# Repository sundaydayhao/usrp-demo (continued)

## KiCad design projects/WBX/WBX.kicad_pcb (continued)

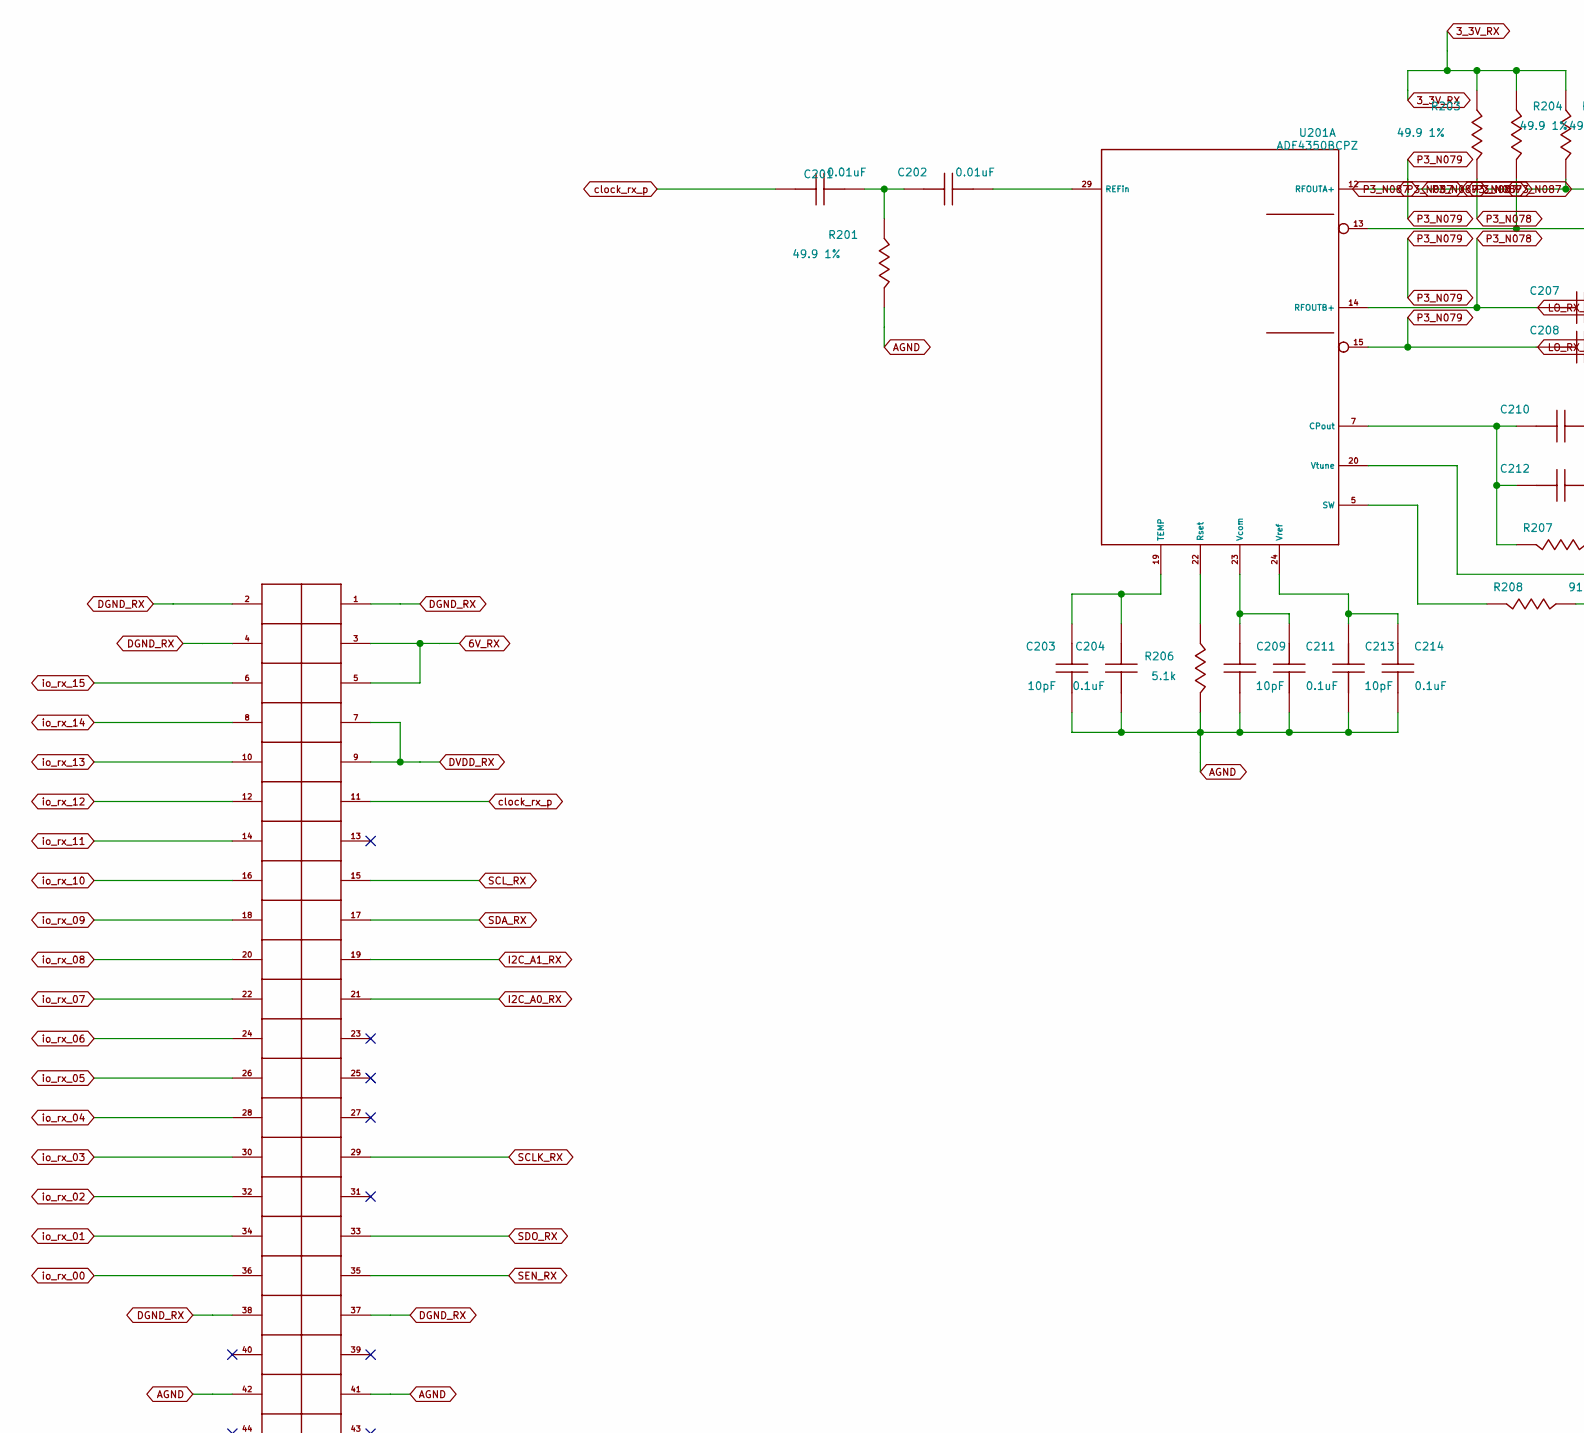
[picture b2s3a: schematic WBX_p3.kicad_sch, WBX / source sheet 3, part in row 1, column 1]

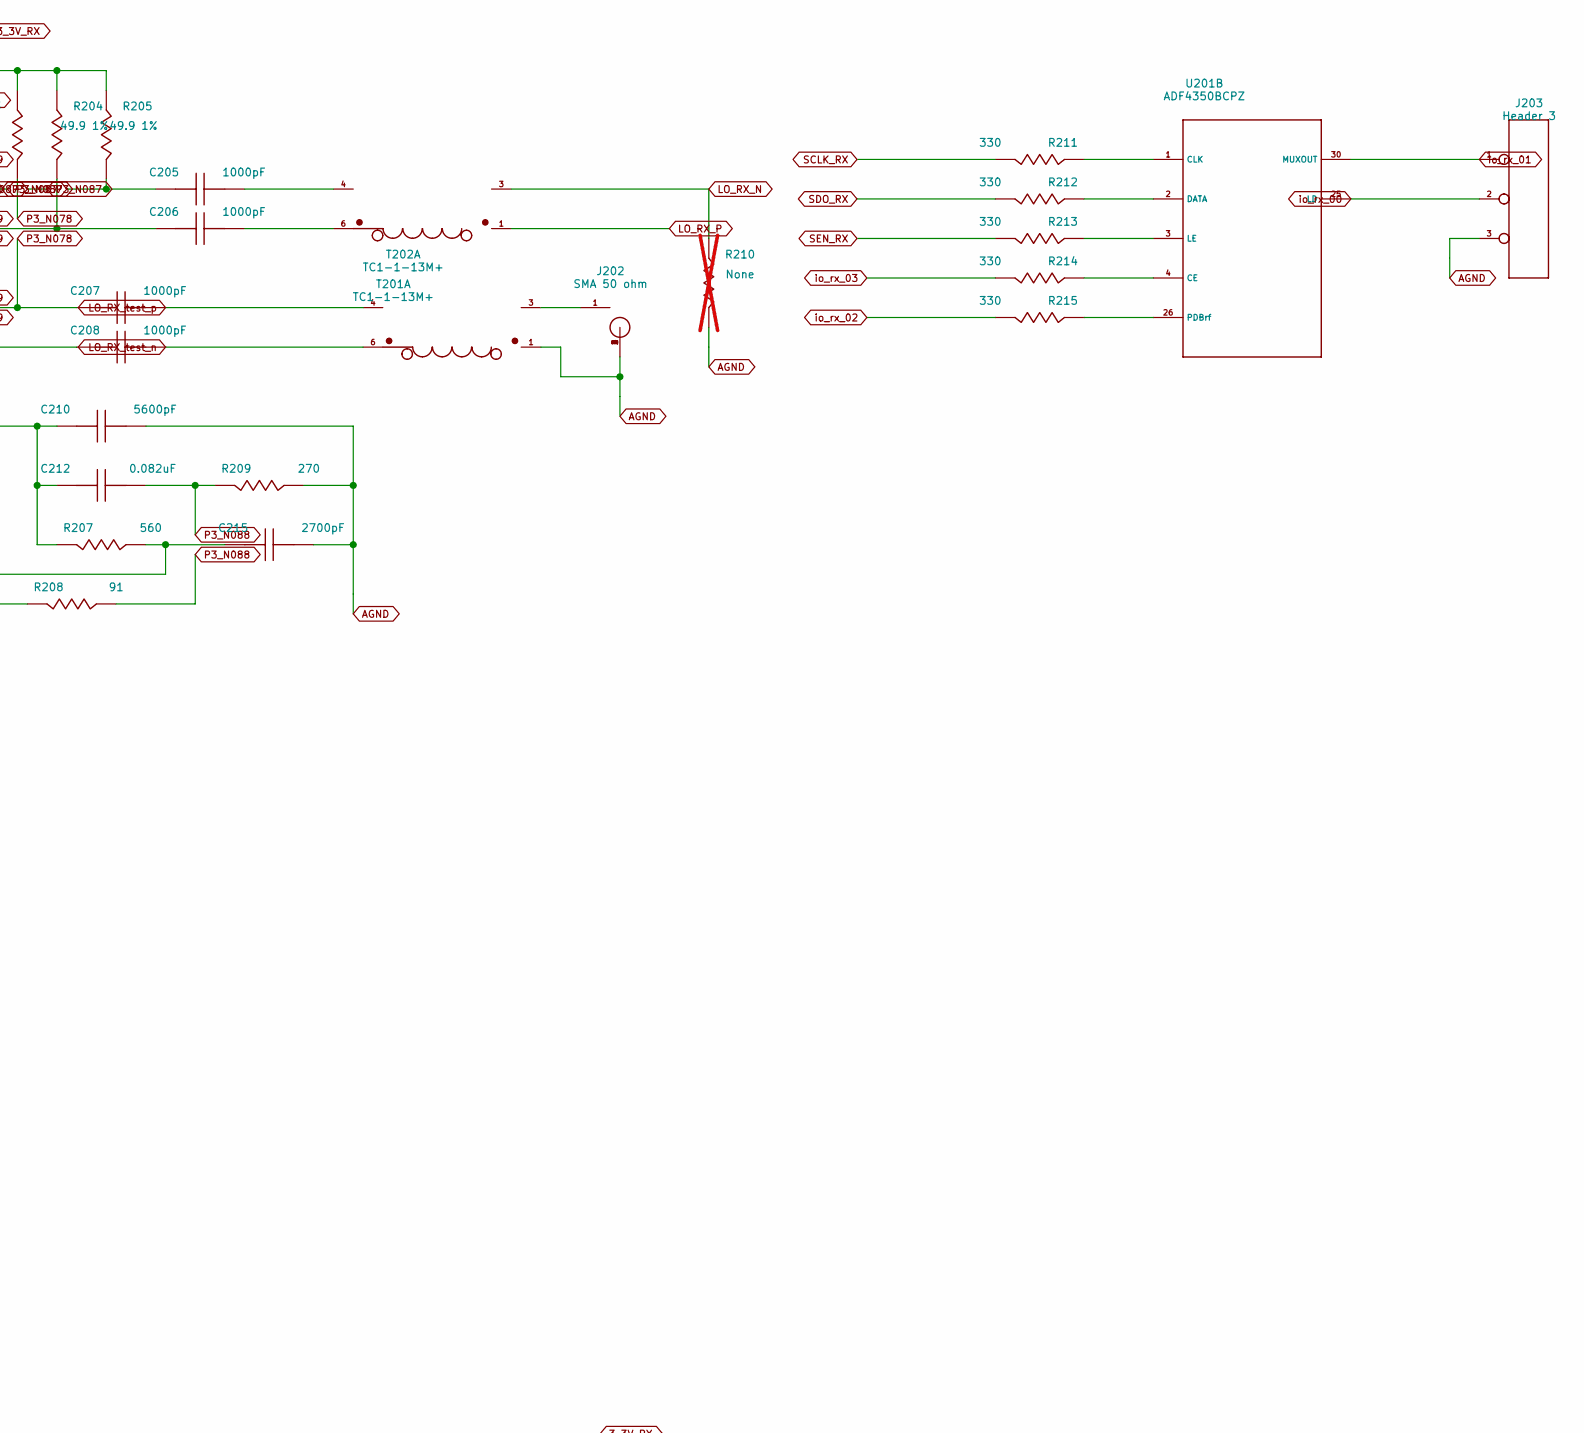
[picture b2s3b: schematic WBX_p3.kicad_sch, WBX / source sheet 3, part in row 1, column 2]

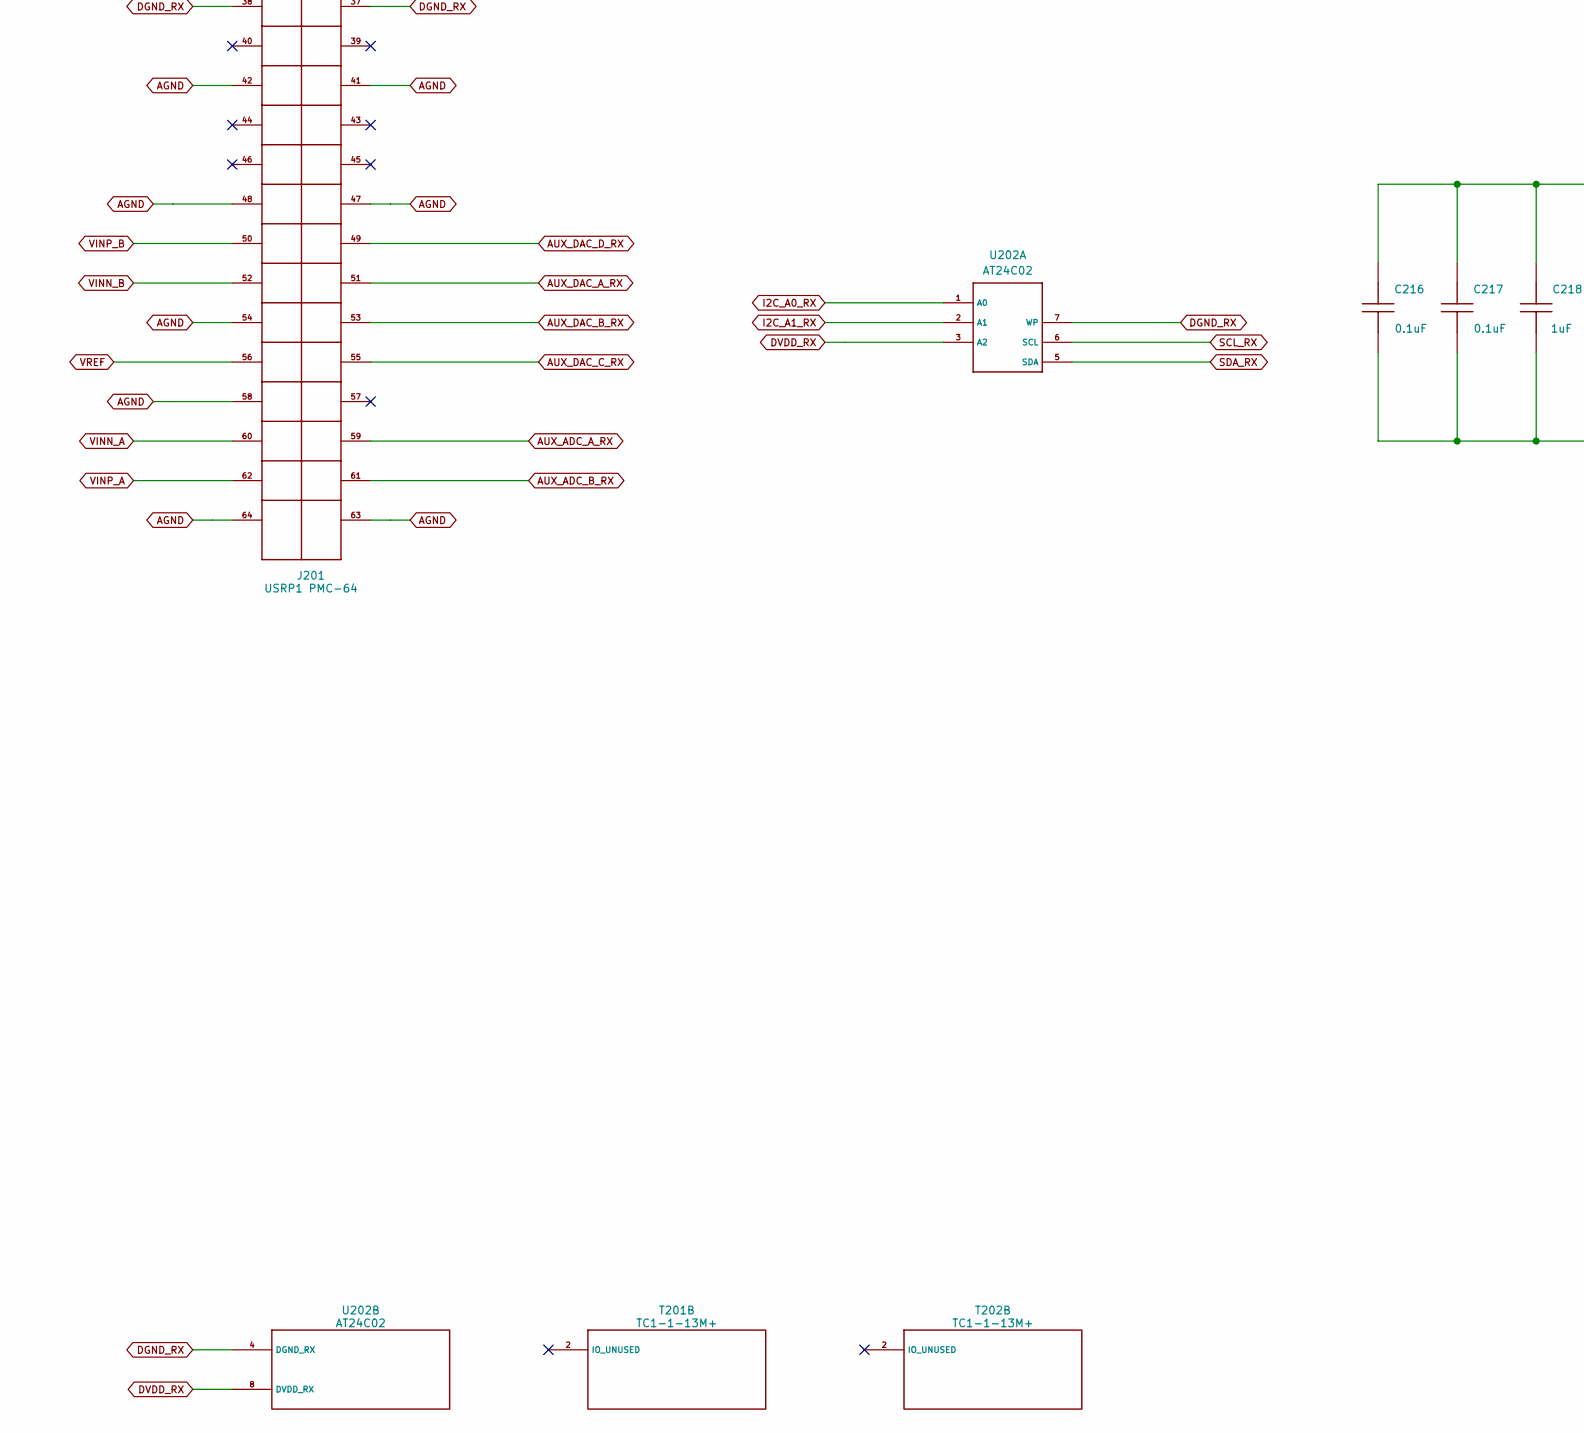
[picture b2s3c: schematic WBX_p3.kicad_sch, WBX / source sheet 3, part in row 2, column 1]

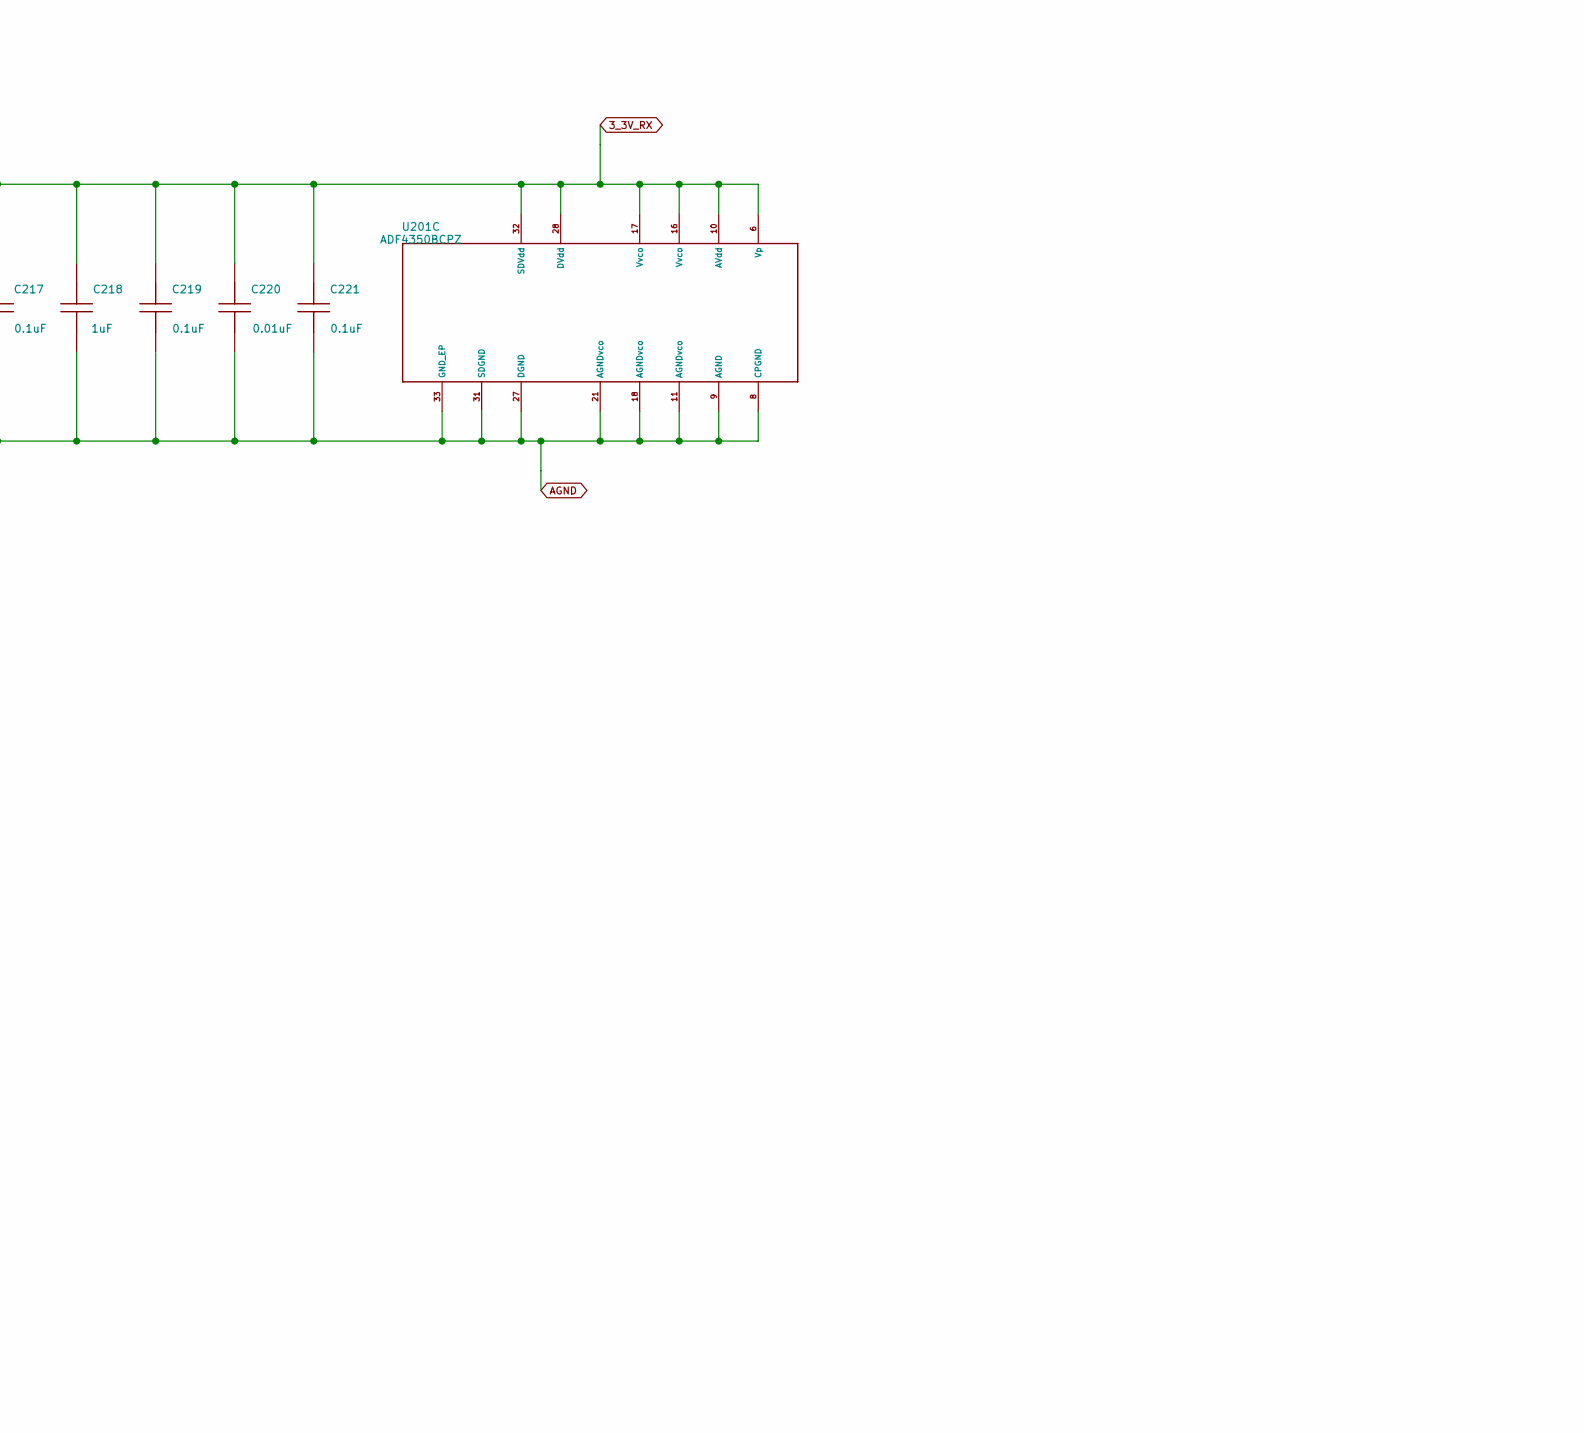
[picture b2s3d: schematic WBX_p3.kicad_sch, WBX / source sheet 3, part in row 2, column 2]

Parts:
C201: 0.01uF; C201
C202: 0.01uF; C202
C203: 10pF; C203
C204: 0.1uF; C204
C205: 1000pF; C205
C206: 1000pF; C206
C207: 1000pF; C207
C208: 1000pF; C208
C209: 10pF; C209
C210: 5600pF; C210
C211: 0.1uF; C211
C212: 0.082uF; C212
C213: 10pF; C213
C214: 0.1uF; C214
C215: 2700pF; C215
C216: 0.1uF; C216; MPN CL05B104KO5NNNC; LCSC C1525
C217: 0.1uF; C217; MPN CL05B104KO5NNNC; LCSC C1525
C218: 1uF; C218
C219: 0.1uF; C219; MPN CL05B104KO5NNNC; LCSC C1525
C220: 0.01uF; C220
C221: 0.1uF; C221; MPN CL05B104KO5NNNC; LCSC C1525
J201: USRP1 PMC-64; J201
J202: SMA 50 ohm; J202
J203: Header 3; J203
R201: 49.9 1%; R201
R203: 49.9 1%; R203
R204: 49.9 1%; R204
R205: 49.9 1%; R205
R206: 5.1k; R206
R207: 560; R207
R208: 91; R208
R209: 270; R209
R210: None; R210; not fitted
R211: 330; R211
R212: 330; R212
R213: 330; R213
R214: 330; R214
R215: 330; R215
T201: TC1-1-13M+; T201; MPN TC1-1-13M+
T202: TC1-1-13M+; T202; MPN TC1-1-13M+
U201: ADF4350BCPZ; U201; MPN ADF4350BCPZ
U202: AT24C02; U202; MPN AT24C02C-SSHM-T; LCSC C6203

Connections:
3_3V_RX: C216.1, C217.1, C218.1, C219.1, C220.1, C221.1, R203.1, R204.1, R205.1, U201.6 (Vp), U201.10 (AVdd), U201.16 (Vvco), U201.17 (Vvco), U201.28 (DVdd), U201.32 (SDVdd); also elsewhere on the board
6V_RX: J201.3, J201.5; also elsewhere on the board
AGND: C203.2, C204.2, C209.2, C210.1, C211.2, C213.2, C214.2, C215.1, C216.2, C217.2, C218.2, C219.2, C220.2, C221.2, J201.41, J201.42, J201.47, J201.48, J201.54, J201.58, J201.63, J201.64, J202.2, J202.3, J202.4, J202.5, J203.3, R201.2, R206.2, R209.1, R210.2, T201.1, U201.8 (CPGND), U201.9 (AGND), U201.11 (AGNDvco), U201.18 (AGNDvco), U201.21 (AGNDvco), U201.27 (DGND), U201.31 (SDGND), U201.33 (GND_EP); also elsewhere on the board
AUX_ADC_A_RX: J201.59; also elsewhere on the board
AUX_ADC_B_RX: J201.61
AUX_DAC_A_RX: J201.51
AUX_DAC_B_RX: J201.53
AUX_DAC_C_RX: J201.55; also elsewhere on the board
AUX_DAC_D_RX: J201.49
DGND_RX: J201.1, J201.2, J201.4, J201.37, J201.38, U202.4 (DGND_RX), U202.7 (WP)
DVDD_RX: J201.7, J201.9, U202.3 (A2), U202.8 (DVDD_RX)
I2C_A0_RX: J201.21, U202.1 (A0)
I2C_A1_RX: J201.19, U202.2 (A1)
LO_RX_N: R210.1, T202.3; also elsewhere on the board
LO_RX_P: T202.1; also elsewhere on the board
LO_RX_test_n: C208.1, T201.6
LO_RX_test_p: C207.1, T201.4
unnamed: C201.1, C202.2, R201.1
unnamed: C205.1, T202.4
unnamed: C206.1, T202.6
unnamed: C206.2, R204.2, U201.13
unnamed: J202.1, T201.3
unnamed: C210.2, C212.2, R207.2, U201.7 (CPout)
unnamed: C202.1, U201.29 (REFin)
unnamed: R206.1, U201.22 (Rset)
unnamed: R208.2, U201.5 (SW)
unnamed: C203.1, C204.1, U201.19 (TEMP)
unnamed: C209.1, C211.1, U201.23 (Vcom)
unnamed: C213.1, C214.1, U201.24 (Vref)
unnamed: C215.2, R207.1, U201.20 (Vtune)
unnamed: R214.1, U201.4 (CE)
unnamed: R211.1, U201.1 (CLK)
unnamed: R212.1, U201.2 (DATA)
unnamed: R213.1, U201.3 (LE)
unnamed: R215.1, U201.26 (PDBrf)
P3_N078: C207.2, R203.2, U201.14 (RFOUTB+)
P3_N079: C208.2, U201.15
P3_N087: C205.2, R205.2, U201.12 (RFOUTA+)
P3_N088: C212.1, R208.1, R209.2
SCLK_RX: J201.29, R211.2
SCL_RX: J201.15, U202.6 (SCL)
SDA_RX: J201.17, U202.5 (SDA)
SDO_RX: J201.33, R212.2
SEN_RX: J201.35, R213.2
VINN_A: J201.60; also elsewhere on the board
VINN_B: J201.52; also elsewhere on the board
VINP_A: J201.62; also elsewhere on the board
VINP_B: J201.50; also elsewhere on the board
VREF: J201.56; also elsewhere on the board
clock_rx_p: C201.2, J201.11
io_rx_00: J201.36, J203.2, U201.25 (LD)
io_rx_01: J201.34, J203.1, U201.30 (MUXOUT)
io_rx_02: J201.32, R215.2
io_rx_03: J201.30, R214.2
io_rx_04: J201.28; also elsewhere on the board
io_rx_05: J201.26; also elsewhere on the board
io_rx_06: J201.24; also elsewhere on the board
io_rx_07: J201.22; also elsewhere on the board
io_rx_08: J201.20; also elsewhere on the board
io_rx_09: J201.18; also elsewhere on the board
io_rx_10: J201.16; also elsewhere on the board
io_rx_11: J201.14; also elsewhere on the board
io_rx_12: J201.12; also elsewhere on the board
io_rx_13: J201.10; also elsewhere on the board
io_rx_14: J201.8; also elsewhere on the board
io_rx_15: J201.6; also elsewhere on the board

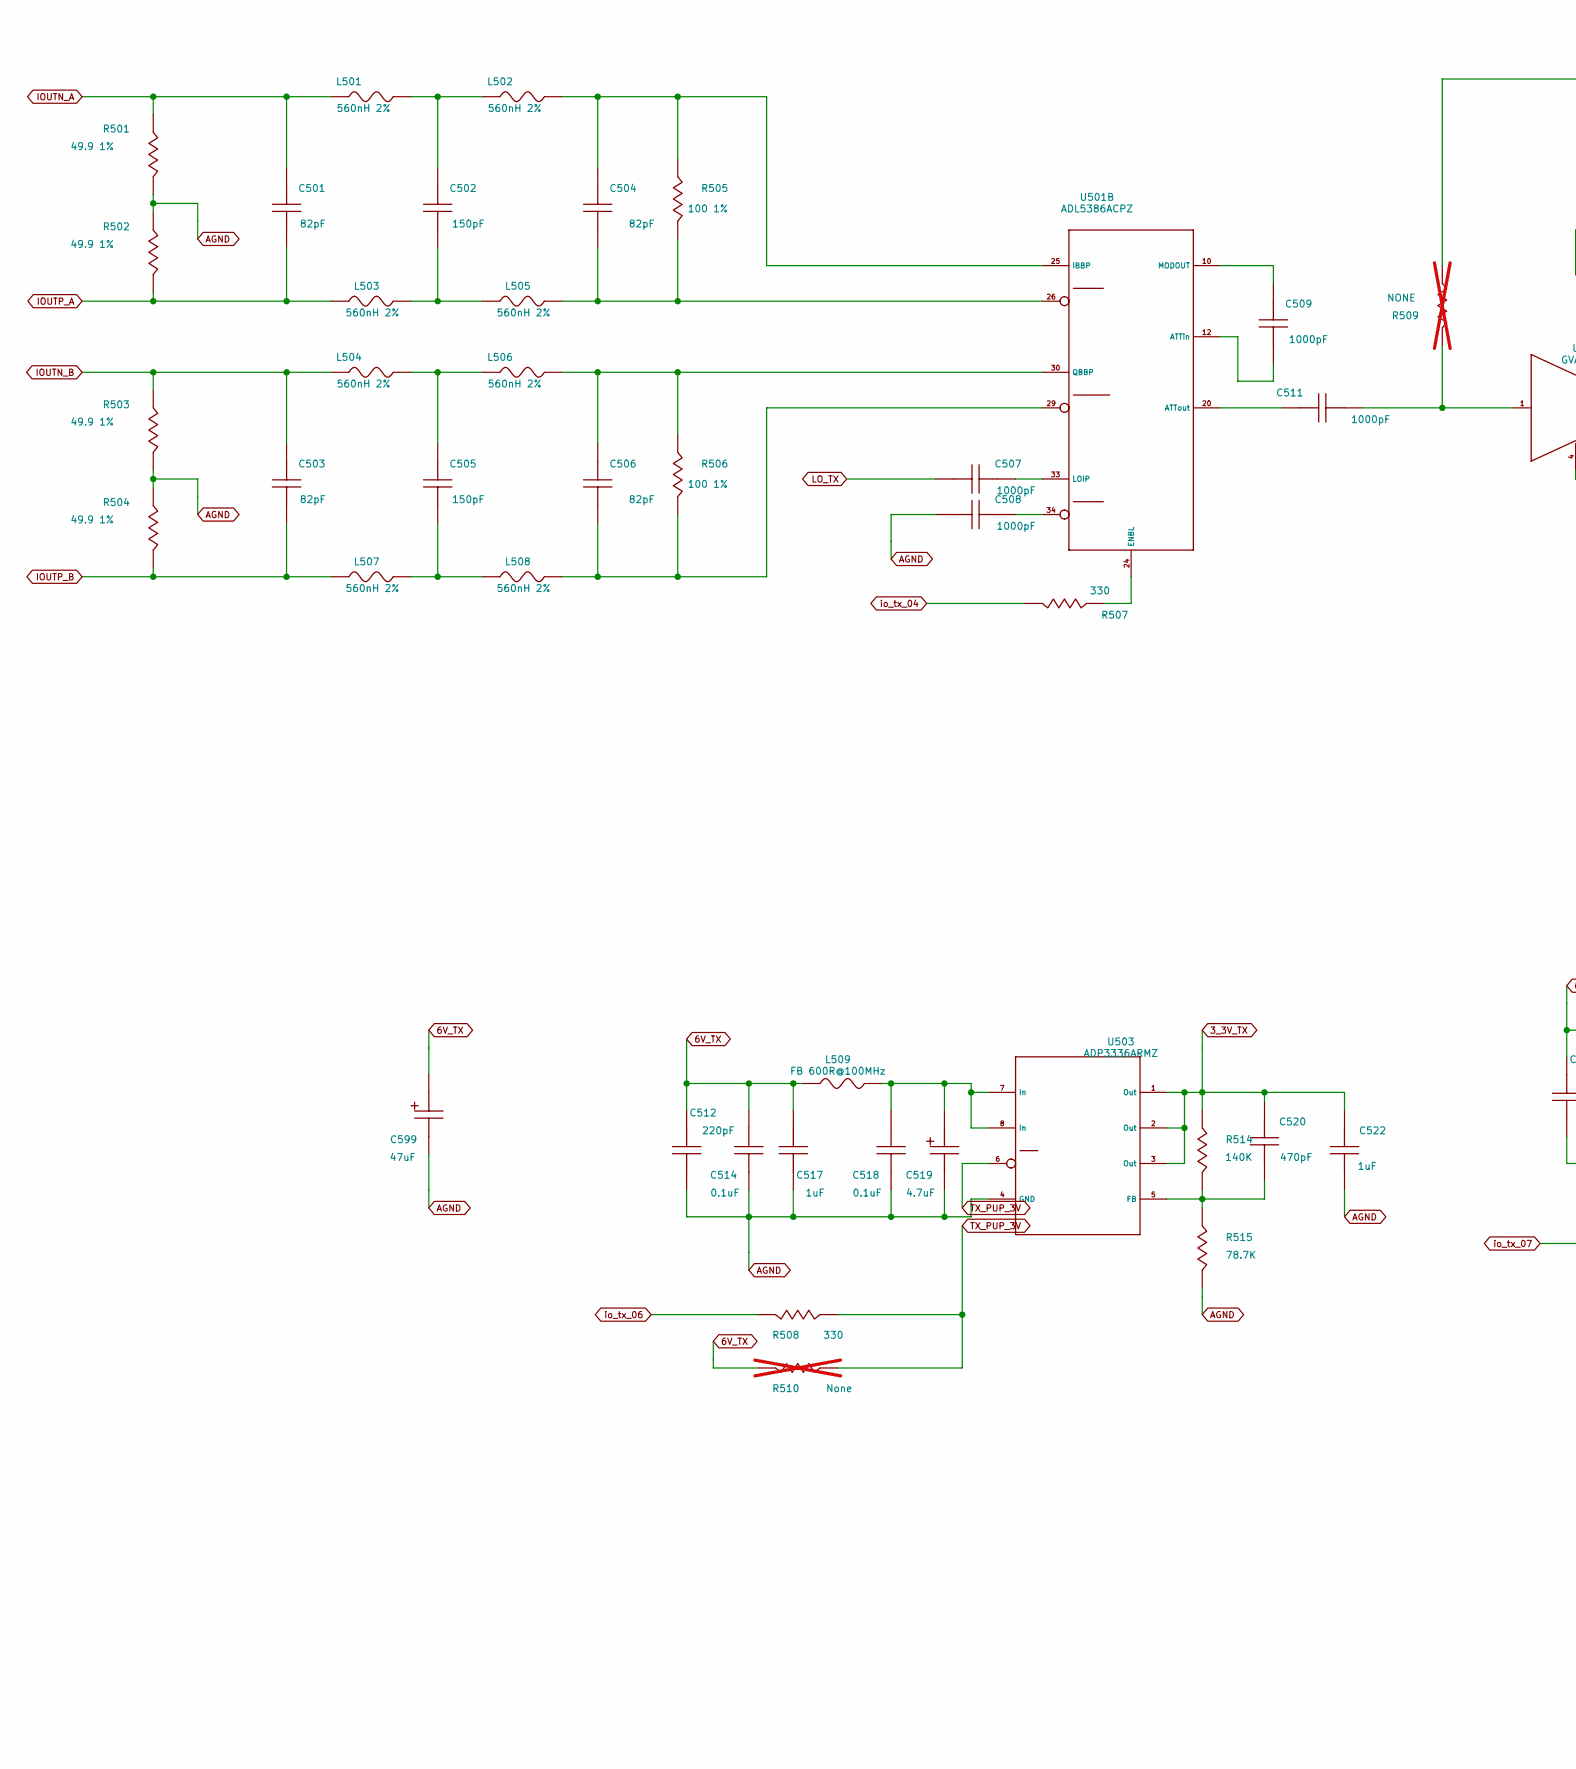
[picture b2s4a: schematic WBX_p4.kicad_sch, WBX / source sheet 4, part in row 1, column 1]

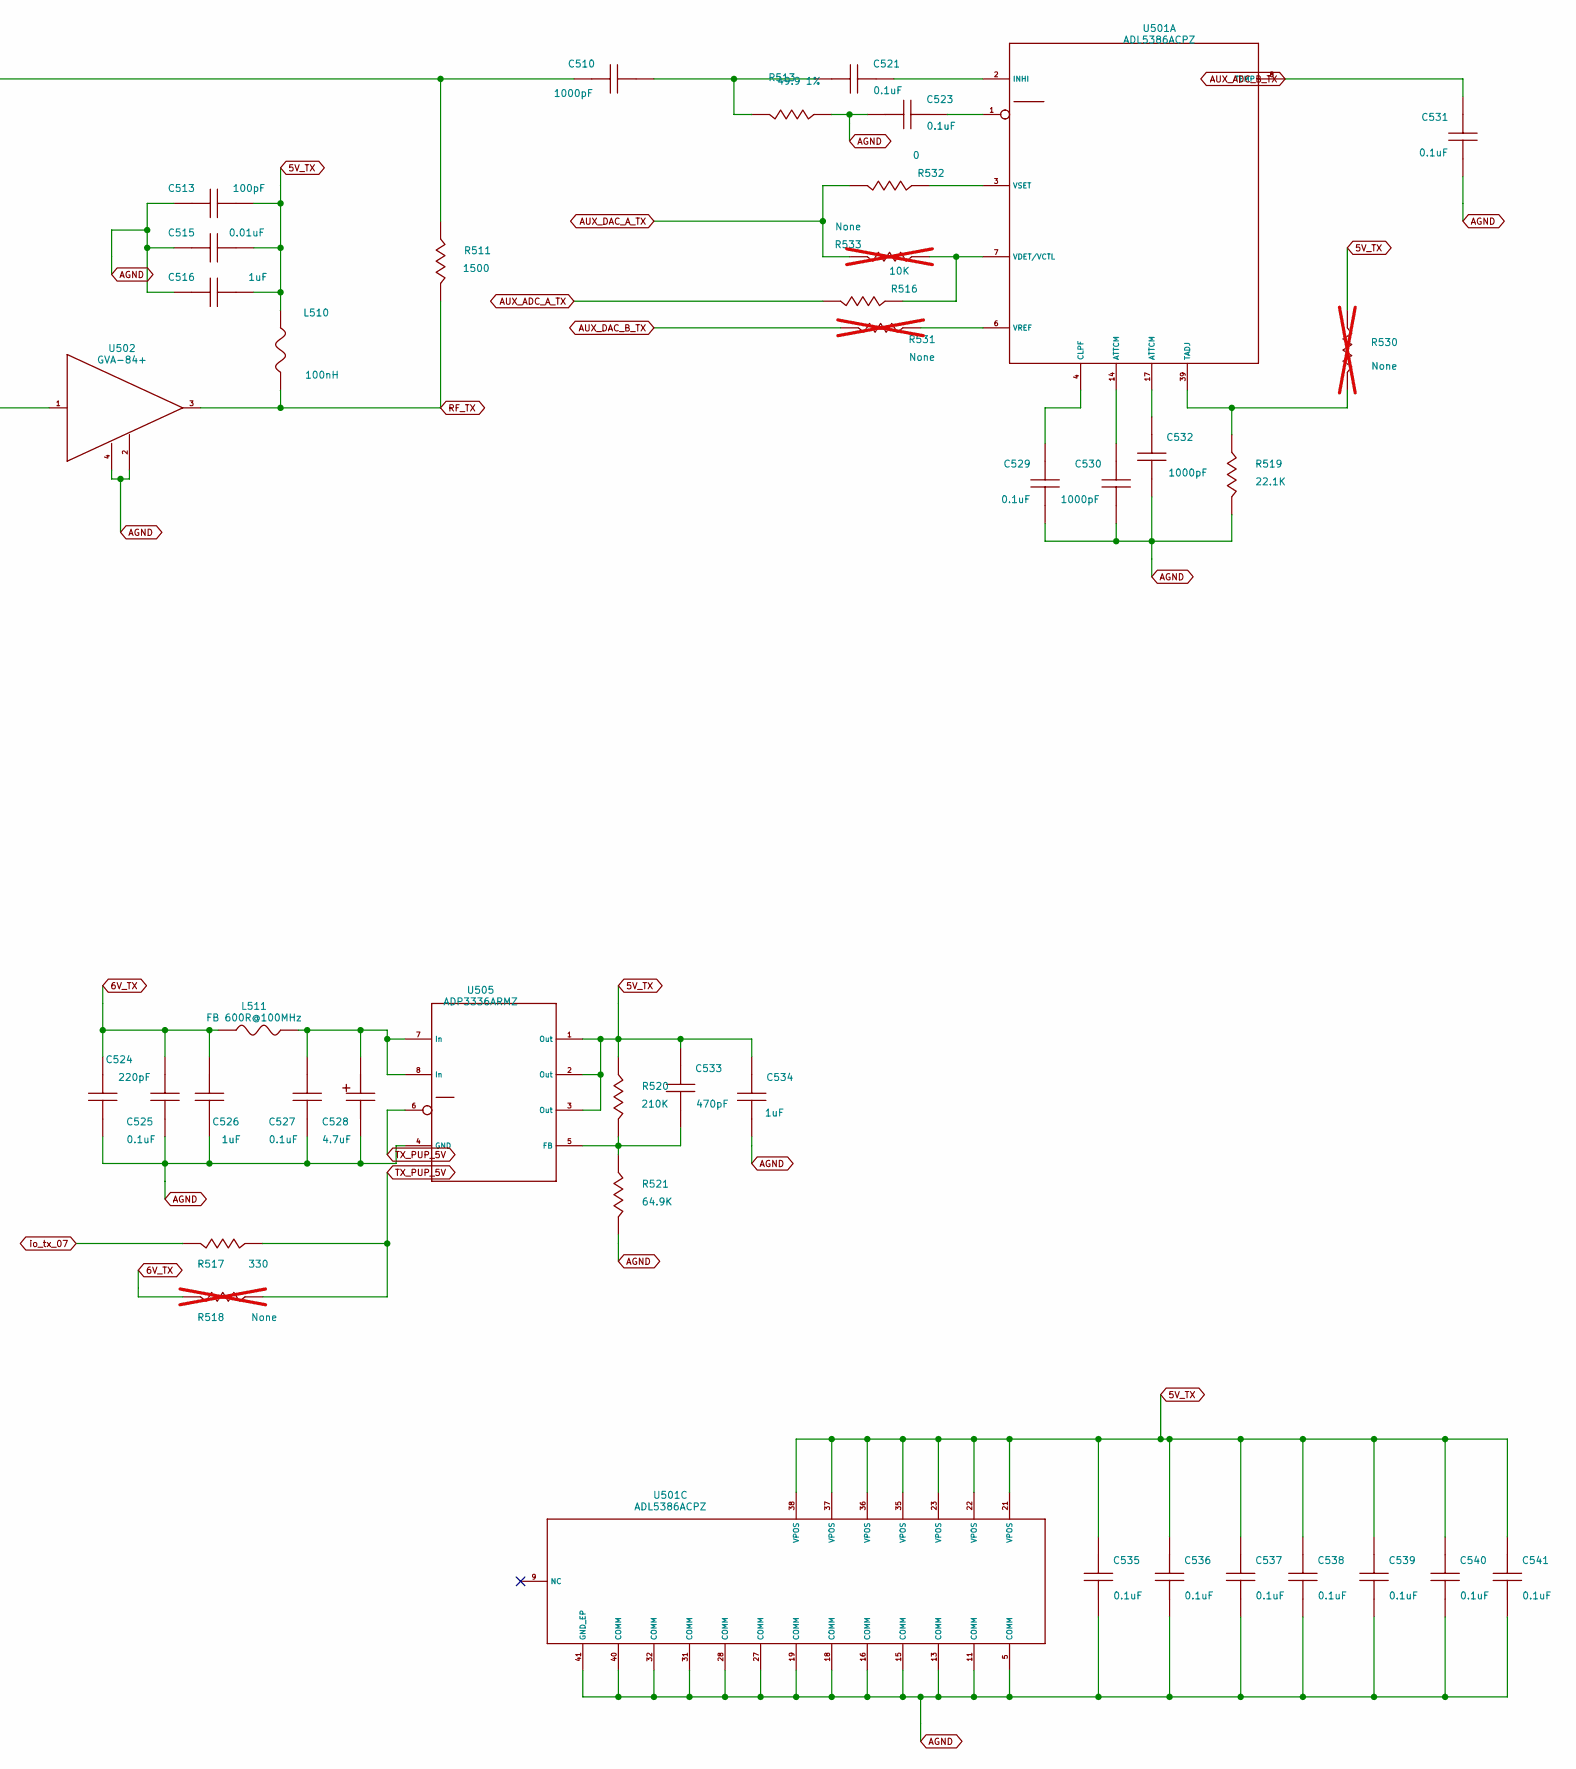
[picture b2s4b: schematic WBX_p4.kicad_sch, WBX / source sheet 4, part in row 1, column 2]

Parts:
C501: 82pF; C501
C502: 150pF; C502
C503: 82pF; C503
C504: 82pF; C504
C505: 150pF; C505
C506: 82pF; C506
C507: 1000pF; C507
C508: 1000pF; C508
C509: 1000pF; C509
C510: 1000pF; C510
C511: 1000pF; C511
C512: 220pF; C512
C513: 100pF; C513
C514: 0.1uF; C514; MPN CL05B104KO5NNNC; LCSC C1525
C515: 0.01uF; C515
C516: 1uF; C516
C517: 1uF; C517
C518: 0.1uF; C518
C519: 4.7uF; C519
C520: 470pF; C520
C521: 0.1uF; C521
C522: 1uF; C522
C523: 0.1uF; C523
C524: 220pF; C524
C525: 0.1uF; C525; MPN CL05B104KO5NNNC; LCSC C1525
C526: 1uF; C526
C527: 0.1uF; C527
C528: 4.7uF; C528
C529: 0.1uF; C529
C530: 1000pF; C530
C531: 0.1uF; C531
C532: 1000pF; C532
C533: 470pF; C533
C534: 1uF; C534
C535: 0.1uF; C535; MPN CL05B104KO5NNNC; LCSC C1525
C536: 0.1uF; C536; MPN CL05B104KO5NNNC; LCSC C1525
C537: 0.1uF; C537; MPN CL05B104KO5NNNC; LCSC C1525
C538: 0.1uF; C538; MPN CL05B104KO5NNNC; LCSC C1525
C539: 0.1uF; C539; MPN CL05B104KO5NNNC; LCSC C1525
C540: 0.1uF; C540; MPN CL05B104KO5NNNC; LCSC C1525
C541: 0.1uF; C541; MPN CL05B104KO5NNNC; LCSC C1525
C599: 47uF; C599
L501: 560nH 2%; L501
L502: 560nH 2%; L502
L503: 560nH 2%; L503
L504: 560nH 2%; L504
L505: 560nH 2%; L505
L506: 560nH 2%; L506
L507: 560nH 2%; L507
L508: 560nH 2%; L508
L509: FB 600R@100MHz; L509
L510: 100nH; L510
L511: FB 600R@100MHz; L511
R501: 49.9 1%; R501
R502: 49.9 1%; R502
R503: 49.9 1%; R503
R504: 49.9 1%; R504
R505: 100 1%; R505
R506: 100 1%; R506
R507: 330; R507
R508: 330; R508
R509: NONE; R509; not fitted
R510: None; R510; not fitted
R511: 1500; R511
R513: 49.9 1%; R513
R514: 140K; R514
R515: 78.7K; R515
R516: 10K; R516
R517: 330; R517
R518: None; R518; not fitted
R519: 22.1K; R519
R520: 210K; R520
R521: 64.9K; R521
R530: None; R530; not fitted
R531: None; R531; not fitted
R532: 0; R532
R533: None; R533; not fitted
U501: ADL5386ACPZ; U501; MPN ADL5386ACPZ
U502: GVA-84+; U502; MPN GVA-84+
U503: ADP3336ARMZ; U503; MPN ADP3336ARMZ
U505: ADP3336ARMZ; U505; MPN ADP3336ARMZ

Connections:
3_3V_TX: C520.1, C522.1, R514.1, U503.1 (Out), U503.2 (Out), U503.3 (Out); also elsewhere on the board
5V_TX: C513.1, C515.1, C516.1, C533.1, C534.1, C535.1, C536.1, C537.1, C538.1, C539.1, C540.1, C541.1, L510.1, R520.1, R530.1, U501.21 (VPOS), U501.22 (VPOS), U501.23 (VPOS), U501.35 (VPOS), U501.36 (VPOS), U501.37 (VPOS), U501.38 (VPOS), U505.1 (Out), U505.2 (Out), U505.3 (Out); also elsewhere on the board
6V_TX: C512.1, C514.1, C517.1, C524.1, C525.1, C526.1, C599.1, L509.2, L511.2, R510.2, R518.2; also elsewhere on the board
AGND: C508.2, C512.2, C513.2, C514.2, C515.2, C516.2, C517.2, C518.2, C519.2, C522.2, C523.2, C524.2, C525.2, C526.2, C527.2, C528.2, C529.2, C530.2, C531.2, C532.2, C534.2, C535.2, C536.2, C537.2, C538.2, C539.2, C540.2, C541.2, C599.2, R501.2, R502.1, R503.2, R504.1, R513.1, R515.2, R519.2, R521.2, U501.5 (COMM), U501.11 (COMM), U501.13 (COMM), U501.15 (COMM), U501.16 (COMM), U501.18 (COMM), U501.19 (COMM), U501.27 (COMM), U501.28 (COMM), U501.31 (COMM), U501.32 (COMM), U501.40 (COMM), U501.41 (GND_EP), U502.2, U502.4, U503.4 (GND), U505.4 (GND); also elsewhere on the board
AUX_ADC_A_TX: R516.2; also elsewhere on the board
AUX_ADC_B_TX: C531.1, U501.8 (TEMP); also elsewhere on the board
AUX_DAC_A_TX: R532.2, R533.2; also elsewhere on the board
AUX_DAC_B_TX: R531.2; also elsewhere on the board
IOUTN_A: C501.1, L501.2, R501.1; also elsewhere on the board
IOUTN_B: C503.1, L504.2, R503.1; also elsewhere on the board
IOUTP_A: C501.2, L503.2, R502.2; also elsewhere on the board
IOUTP_B: C503.2, L507.2, R504.2; also elsewhere on the board
LO_TX: C507.2; also elsewhere on the board
unnamed: C502.1, L501.1, L502.2
unnamed: C502.2, L503.1, L505.2
unnamed: C504.2, L505.1, R505.2, U501.26
unnamed: C505.1, L504.1, L506.2
unnamed: C505.2, L507.1, L508.2
unnamed: C506.2, L508.1, R506.2, U501.29
unnamed: C508.1, U501.34
unnamed: C510.1, C521.2, R513.2
unnamed: C510.2, R509.1, R511.1
unnamed: C511.1, R509.2, U502.1
unnamed: C518.1, C519.1, L509.1, U503.7 (In), U503.8 (In)
unnamed: C523.1, U501.1
unnamed: C527.1, C528.1, L511.1, U505.7 (In), U505.8 (In)
unnamed: C530.1, U501.14 (ATTCM)
unnamed: C532.1, U501.17 (ATTCM)
unnamed: C529.1, U501.4 (CLPF)
unnamed: C521.1, U501.2 (INHI)
unnamed: R519.1, R530.2, U501.39 (TADJ)
unnamed: R516.1, R533.1, U501.7 (VDET/VCTL)
unnamed: R531.1, U501.6 (VREF)
unnamed: R532.1, U501.3 (VSET)
unnamed: C509.2, U501.12 (ATTin)
unnamed: C511.2, U501.20 (ATTout)
unnamed: R507.1, U501.24 (ENBL)
unnamed: C504.1, L502.1, R505.1, U501.25 (IBBP)
unnamed: C507.1, U501.33 (LOIP)
unnamed: C509.1, U501.10 (MODOUT)
unnamed: C506.1, L506.1, R506.1, U501.30 (QBBP)
unnamed: C520.2, R514.2, R515.1, U503.5 (FB)
unnamed: C533.2, R520.2, R521.1, U505.5 (FB)
RF_TX: L510.2, R511.2, U502.3; also elsewhere on the board
TX_PUP_3V: R508.1, R510.1, U503.6
TX_PUP_5V: R517.1, R518.1, U505.6
io_tx_04: R507.2; also elsewhere on the board
io_tx_06: R508.2; also elsewhere on the board
io_tx_07: R517.2; also elsewhere on the board
